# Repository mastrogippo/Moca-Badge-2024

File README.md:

# Moca Badge 2024

A back-to-the-r00t badge for soldering practice

# Breadboard

Looks like a breadboard, works like a breadboard. 

Switch 3 connects battery positive to the bottom row, switch 4 connects battery negative to the second row from the bottom.

# LED sections
## Easy

3 rows of ten 0805 LED and resistor pair, controlled by switch 2. 

## Hard

Think you can solder all the way down to 0201 components? Turn them on with switch 1.

# Battery

A regular CR2032. 

WARNING: When inserting the CR2032 battery, angle it at 45° under the terminals before pushing it down.

Battery Removal:
When removing the battery, use a lever between the battery and the holder. Do not place the lever between the battery and the PCB to avoid ripping off the solder joints.

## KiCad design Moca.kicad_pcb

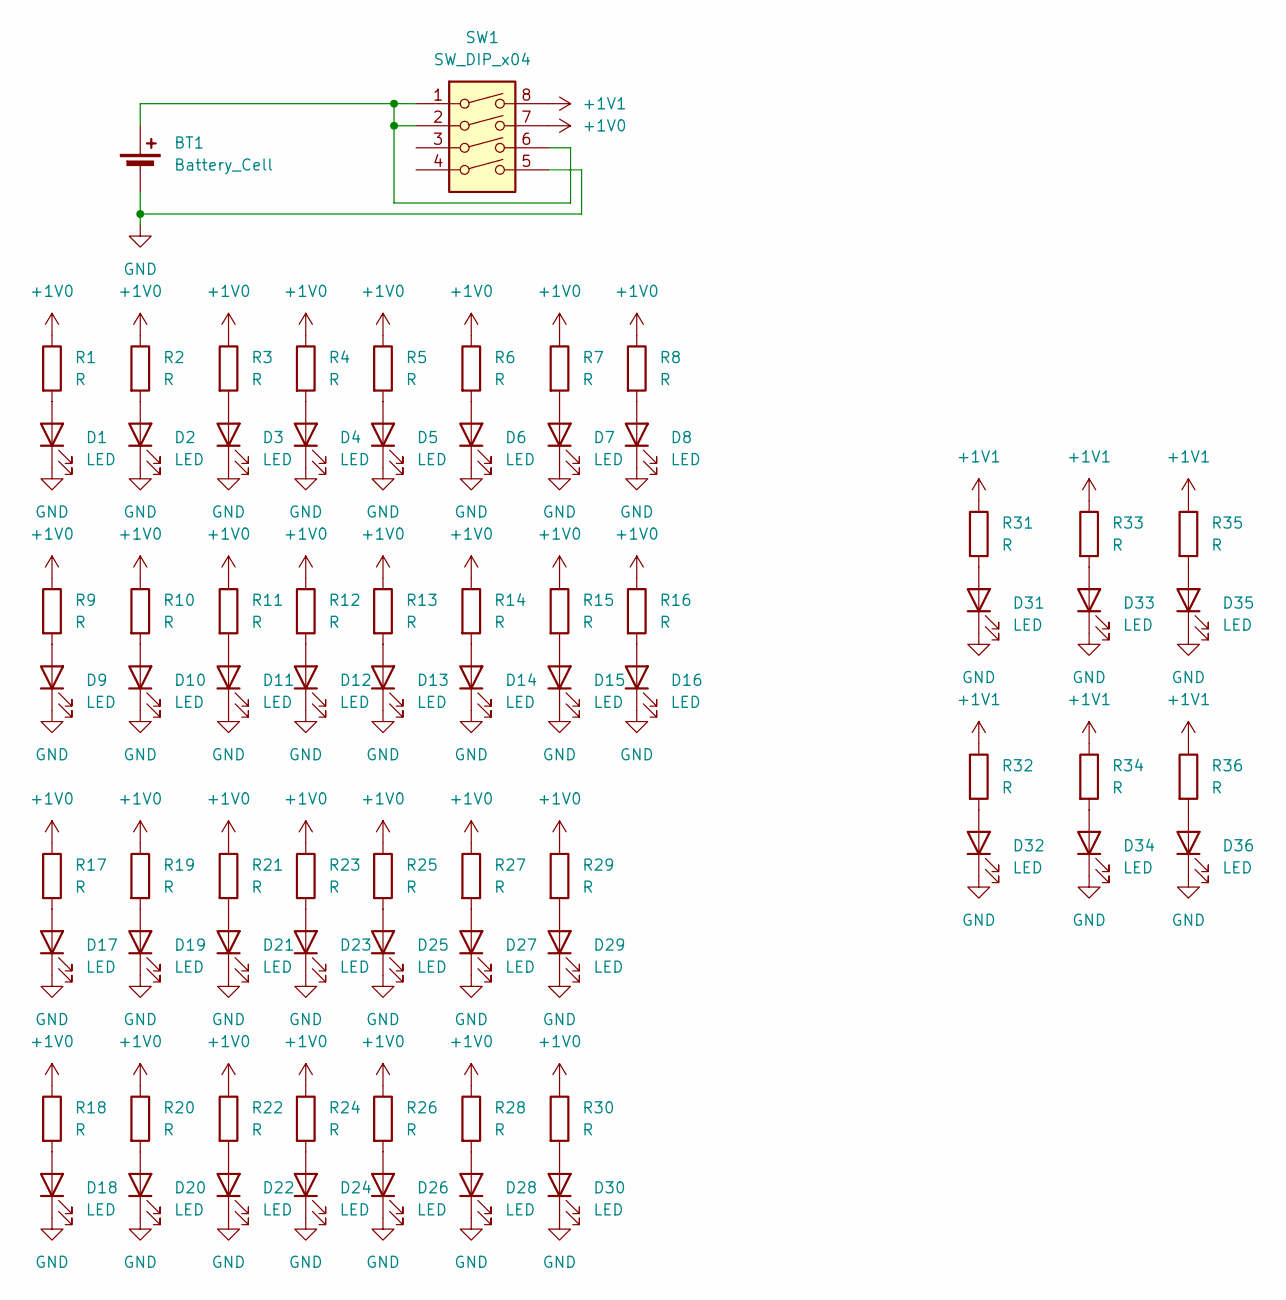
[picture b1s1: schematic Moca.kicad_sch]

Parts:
BT1: Battery_Cell; BatteryHolder_Keystone_1060_1x2032
D1, D2, D3, D4, D5, D6, D7, D8, D9, D10, D11, D12, D13, D14, D15, D16, D17, D18, D19, D20, D21, D22, D23, D24, D25, D26, D27, D28, D29, D30: LED; LED_0805_2012Metric_Pad1.15x1.40mm_HandSolder
D31, D32: LED; LED_0603_1608Metric_Pad1.05x0.95mm_HandSolder
D33, D34: LED; LED_0402_1005Metric_Pad0.77x0.64mm_HandSolder
D35, D36: LED; LED_0201_0603Metric_Pad0.64x0.40mm_HandSolder
R1, R2, R3, R4, R5, R6, R7, R8, R9, R10, R11, R12, R13, R14, R15, R16, R17, R18, R19, R20, R21, R22, R23, R24, R25, R26, R27, R28, R29, R30: R; R_0805_2012Metric_Pad1.20x1.40mm_HandSolder
R31, R32: R; R_0603_1608Metric_Pad0.98x0.95mm_HandSolder
R33, R34: R; R_0402_1005Metric_Pad0.72x0.64mm_HandSolder
R35, R36: R; R_0201_0603Metric_Pad0.64x0.40mm_HandSolder
SW1: SW_DIP_x04; SW_DIP_SPSTx04_Slide_9.78x12.34mm_W7.62mm_P2.54mm

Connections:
+1V0: R1.1, R2.1, R3.1, R4.1, R5.1, R6.1, R7.1, R8.1, R9.1, R10.1, R11.1, R12.1, R13.1, R14.1, R15.1, R16.1, R17.1, R18.1, R19.1, R20.1, R21.1, R22.1, R23.1, R24.1, R25.1, R26.1, R27.1, R28.1, R29.1, R30.1, SW1.7
+1V1: R31.1, R32.1, R33.1, R34.1, R35.1, R36.1, SW1.8
GND: BT1.2 (-), D1.1 (K), D2.1 (K), D3.1 (K), D4.1 (K), D5.1 (K), D6.1 (K), D7.1 (K), D8.1 (K), D9.1 (K), D10.1 (K), D11.1 (K), D12.1 (K), D13.1 (K), D14.1 (K), D15.1 (K), D16.1 (K), D17.1 (K), D18.1 (K), D19.1 (K), D20.1 (K), D21.1 (K), D22.1 (K), D23.1 (K), D24.1 (K), D25.1 (K), D26.1 (K), D27.1 (K), D28.1 (K), D29.1 (K), D30.1 (K), D31.1 (K), D32.1 (K), D33.1 (K), D34.1 (K), D35.1 (K), D36.1 (K), SW1.5
unnamed: BT1.1 (+), SW1.1, SW1.2, SW1.6
unnamed: D1.2 (A), R1.2
unnamed: D2.2 (A), R2.2
unnamed: D3.2 (A), R3.2
unnamed: D4.2 (A), R4.2
unnamed: D5.2 (A), R5.2
unnamed: D6.2 (A), R6.2
unnamed: D7.2 (A), R7.2
unnamed: D8.2 (A), R8.2
unnamed: D9.2 (A), R9.2
unnamed: D10.2 (A), R10.2
unnamed: D11.2 (A), R11.2
unnamed: D12.2 (A), R12.2
unnamed: D13.2 (A), R13.2
unnamed: D14.2 (A), R14.2
unnamed: D15.2 (A), R15.2
unnamed: D16.2 (A), R16.2
unnamed: D17.2 (A), R17.2
unnamed: D18.2 (A), R18.2
unnamed: D19.2 (A), R19.2
unnamed: D20.2 (A), R20.2
unnamed: D21.2 (A), R21.2
unnamed: D22.2 (A), R22.2
unnamed: D23.2 (A), R23.2
unnamed: D24.2 (A), R24.2
unnamed: D25.2 (A), R25.2
unnamed: D26.2 (A), R26.2
unnamed: D27.2 (A), R27.2
unnamed: D28.2 (A), R28.2
unnamed: D29.2 (A), R29.2
unnamed: D30.2 (A), R30.2
unnamed: D31.2 (A), R31.2
unnamed: D32.2 (A), R32.2
unnamed: D33.2 (A), R33.2
unnamed: D34.2 (A), R34.2
unnamed: D35.2 (A), R35.2
unnamed: D36.2 (A), R36.2

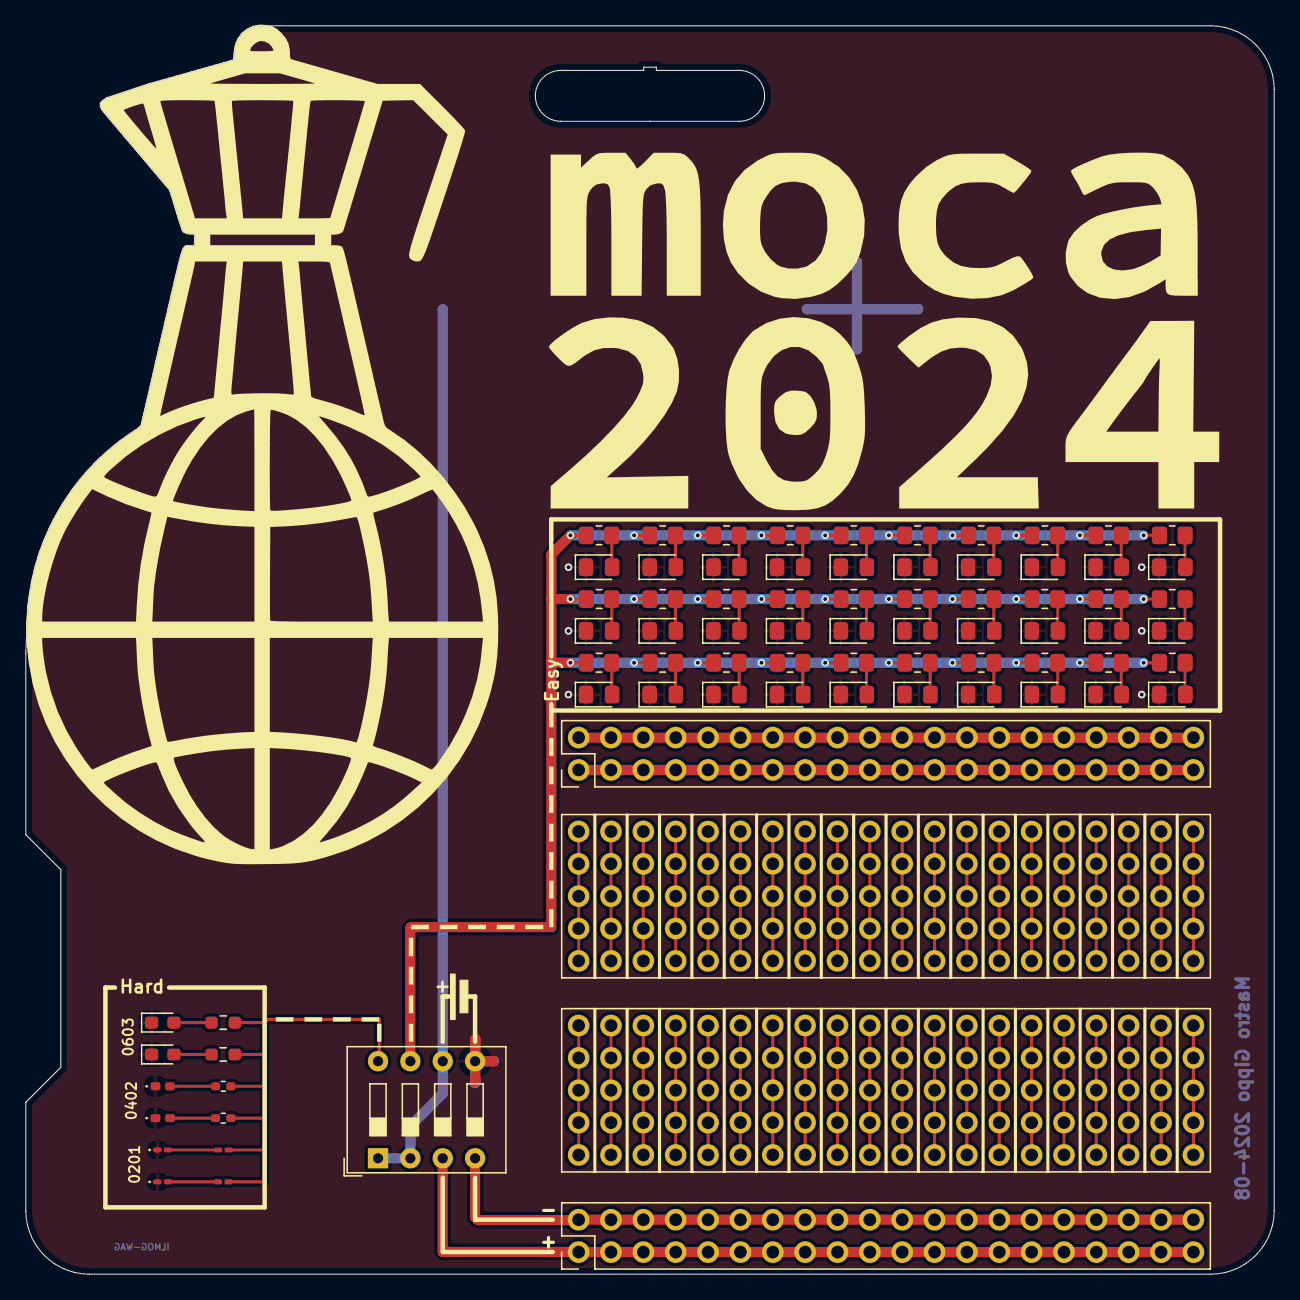
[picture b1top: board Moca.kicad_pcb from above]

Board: 2 copper layers, 98.0 x 98.0 mm, 74 parts (1 on the bottom side), 40 nets.

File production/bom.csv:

Designator,Footprint,Quantity,Value,LCSC Part #
BT1,BatteryHolder_Keystone_1060_1x2032,1,Battery_Cell,
"D1, D10, D11, D12, D13, D14, D15, D16, D17, D18, D19, D2, D20, D21, D22, D23, D24, D25, D26, D27, D28, D29, D3, D30, D4, D5, D6, D7, D8, D9",0805,30,LED,
"D31, D32",0603,2,LED,
"D33, D34",0402,2,LED,
"D35, D36",0201,2,LED,
"R1, R10, R11, R12, R13, R14, R15, R16, R17, R18, R19, R2, R20, R21, R22, R23, R24, R25, R26, R27, R28, R29, R3, R30, R4, R5, R6, R7, R8, R9",0805,30,R,
"R31, R32",0603,2,R,
"R33, R34",0402,2,R,
"R35, R36",0201,2,R,
SW1,SW_DIP_SPSTx04_Slide_9.78x12.34mm_W7.62mm_P2.54mm,1,SW_DIP_x04,

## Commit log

2024-10-03 Production files
2024-10-08 Update README.md
    add battery insertion image
